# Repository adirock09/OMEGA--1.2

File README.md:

# OMEGA--1.2<br><br>
<br><br>

This is a Custom Rp2040 Chip Based MicroPad , It has 9 Switches , a roter encode and a oled screen . We used matrix for switches so it uses less gpio pins and it has 4 layers the rotor key is used to change the layers which is displaced on the screen so in total we have  keys output 9x4=36 + 4 outputs from rotor = 40 Outputs.
## Features

- Based on RP2040 Chip
- Has total 40 Outputs
## Firmware
- Firmware is based on QMK.
### Schematic<br><br>
<br><br>

###  PCB Design<br><br>
<br><br>
### Case<br><br>

<br><br>

### 3D Design<br><br>

<br><br>

#  Bill of Materials (BOM)

##  DigiKey Components

| Qty | Manufacturer Part Number | Description | Unit Price (USD) | Total (USD) |
|-----|--------------------------|-------------|------------------|-------------|
| 2 | C0402C105K9PACTU | 1µF 6.3V X5R Capacitor (0402) | 0.08000 | 0.16 |
| 11 | 0402B104K160CT | 0.1µF 16V X7R Capacitor (0402) | 0.00300 | 0.03 |
| 2 | LMK107BBJ106MALT | 10µF 10V X5R Capacitor (0603) | 0.08000 | 0.16 |
| 2 | CL05C330JB5NNNC | 33pF 50V C0G Capacitor (0402) | 0.10000 | 0.20 |
| 1 | USB4215-03-A | USB Type-C Receptacle (USB 2.0) | 0.49000 | 0.49 |
| 2 | RC0402FR-075K1L | 5.1KΩ 1% Resistor (0402) | 0.10000 | 0.20 |
| 2 | ERA-2AEB273X | 27KΩ 0.1% Resistor (0402) | 0.10000 | 0.20 |
| 1 | 18996 | 0.91" OLED Display Module | 1.95 | 1.95 |
| 2 | RMCF0603FT1K00 | 1KΩ 1% Resistor (0603) | 0.10000 | 0.20 |
| 1 | RC0201FR-0710KL | 10KΩ 1% Resistor (0201) | 0.10000 | 0.10 |
| 1 | SW-PB9-AB00AQE-5 | Subminiature Pushbutton Switch | 3.39000 | 3.39 |
| 1 | SC0914(13) | RP2040 Microcontroller (QFN-56) | 0.70000 | 0.70 |
| 1 | MCP1700T-3302E/TT | 3.3V 250mA Linear Voltage Regulator | 0.51000 | 0.51 |
| 1 | AT24CS02-SSHM-T | 2Kbit I2C EEPROM | 0.31000 | 0.31 |
| 1 | STDCRA3-8M | 8MHz SMD Crystal | 0.84000 | 0.84 |
| 1 | 183031570409 | M3 Hex Socket Cap Screw | 5.05000 | 5.05 |
| 1 | 5009 | DSA Keycap Set (MX Compatible) | 5.95000 | 5.95 |
| 5 | DV-M30-TH | M3 Heat-Set Thread Insert | 0.18200 | 0.91 |
| 9 | MX2A-71NW | Cherry MX Silent Red Switch | 1.95000 | 17.55 |
| 10 | 1N4148 | Signal Diode 100V 200mA | 0.03900 | 0.39 |
| 1 | 6071183 | Rotary Encoder (BCG13 Series) | 2.44000 | 2.44 |

---

##  Manufacturing & Shipping

| Item | Cost (USD) |
|------|------------|
| DigiKey Shipping  | 20.00 |
| JLCPCB – PCB Fabrication + Stencil | 7.01 |
| JLCPCB Shipping - Coupons | 8.16 |

---

#  Total Project Cost

| Category | Cost (USD) |
|----------|------------|
| DigiKey Components | 41.73 |
| DigiKey Shipping | 20.00 |
| JLCPCB PCB + Stencil | 7.01 |
| JLCPCB Shipping - Coupons | 8.16|
| **Grand Total** | **76.9 USD** |

---

##  Final Total: **$76.9 USD**

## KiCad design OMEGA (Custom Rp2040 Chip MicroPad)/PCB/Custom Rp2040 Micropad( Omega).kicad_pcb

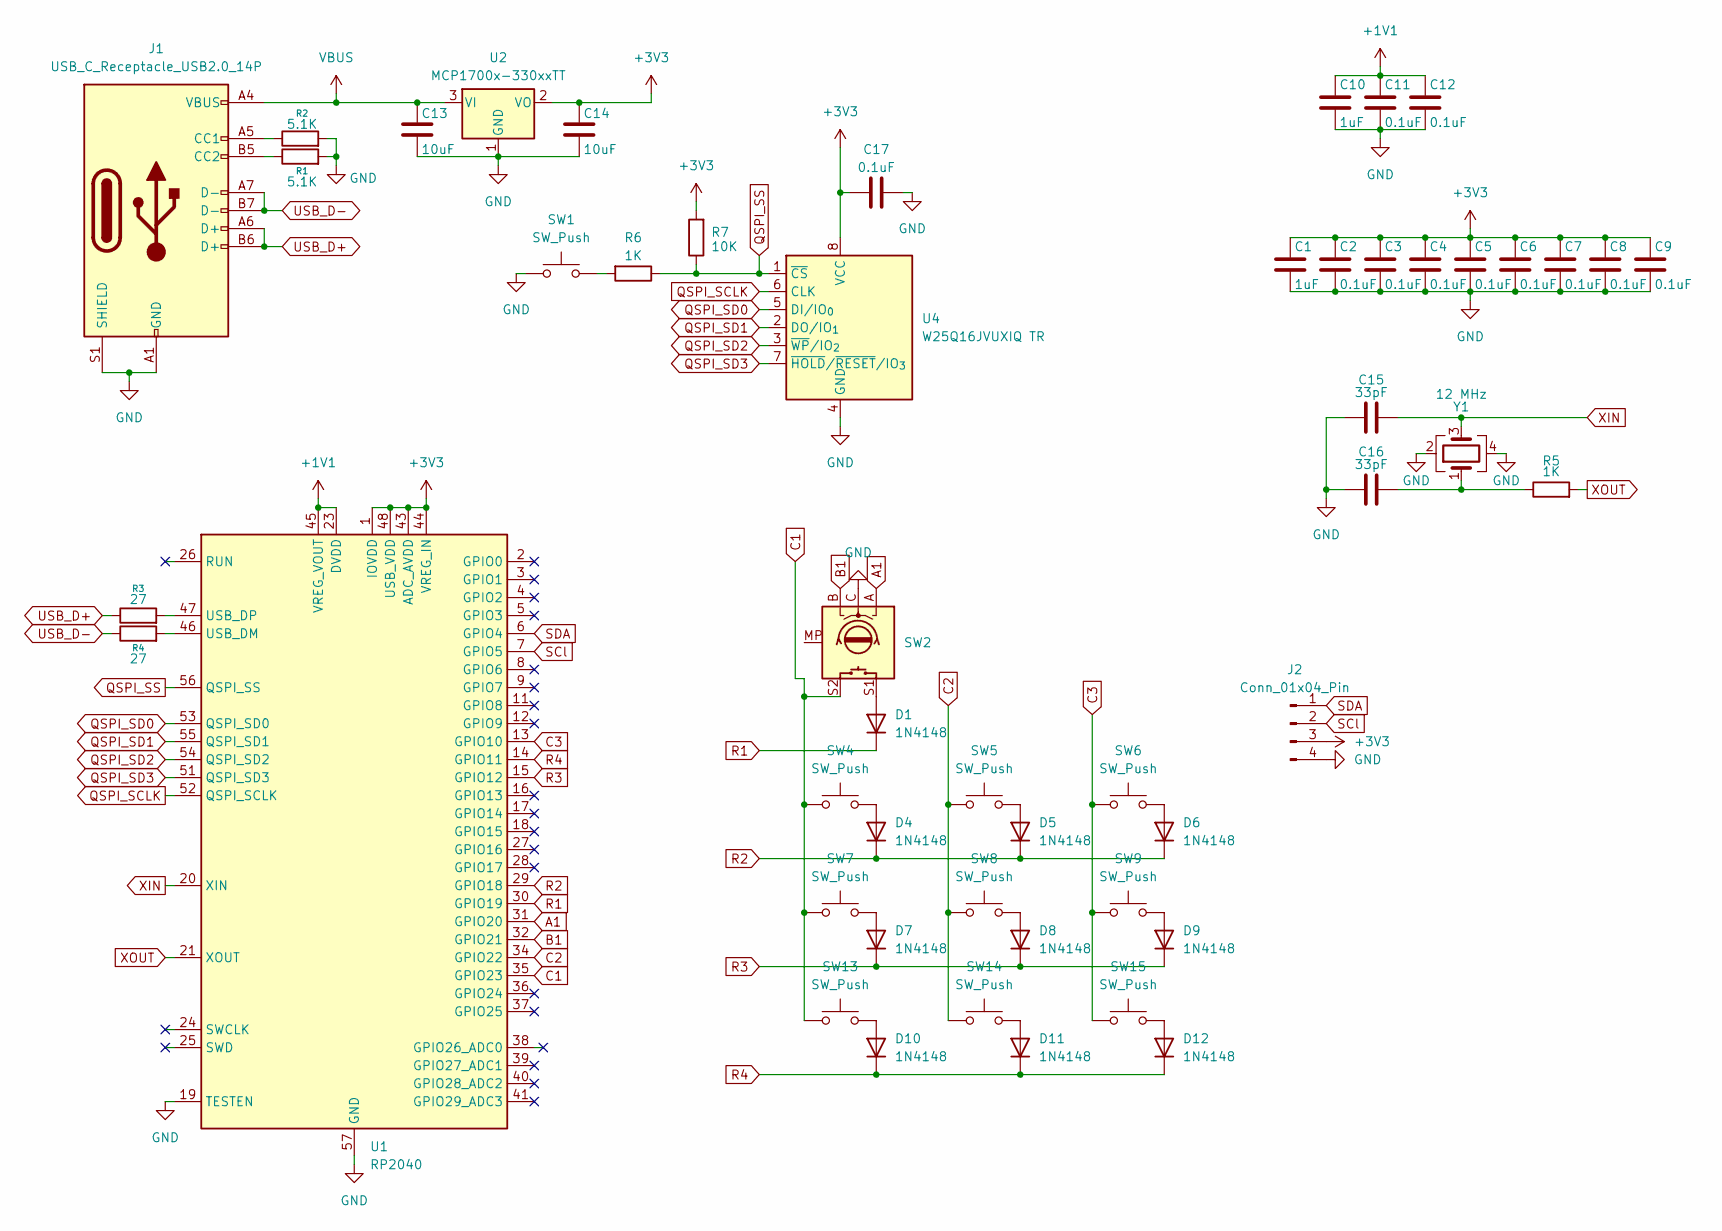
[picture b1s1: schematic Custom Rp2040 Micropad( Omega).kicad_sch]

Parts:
C1, C10: 1uF; C_0402_1005Metric
C2, C3, C4, C5, C6, C7, C8, C9, C11, C12, C17: 0.1uF; C_0402_1005Metric
C13, C14: 10uF; C_0603_1608Metric
C15, C16: 33pF; C_0402_1005Metric
D1, D4, D5, D6, D7, D8, D9, D10, D11, D12: 1N4148; D_DO-35_SOD27_P7.62mm_Horizontal
J1: USB_C_Receptacle_USB2.0_14P; USB_C_Receptacle_HRO_TYPE-C-31-M-12
J2: Conn_01x04_Pin; OLED_128x32
R1, R2: 5.1K; R_0402_1005Metric
R3, R4: 27; R_0402_1005Metric
R5, R6: 1K; R_0402_1005Metric
R7: 10K; R_0402_1005Metric
SW1: SW_Push; SW_Push_SPST_NO_Alps_SKRK
SW2: RotaryEncoder_Switch_MP; RotaryEncoder_Alps_EC11E-Switch_Vertical_H20mm
SW4, SW5, SW6, SW7, SW8, SW9, SW13, SW14, SW15: SW_Push; SW_Cherry_MX_1.00u_PCB
U1: RP2040; QFN-56-1EP_7x7mm_P0.4mm_EP3.2x3.2mm
U2: MCP1700x-330xxTT; SOT-23
U4: W25Q16JVUXIQ TR; Winbond_USON-8-1EP_3x2mm_P0.5mm_EP0.2x1.6mm
Y1: 12 MHz; Crystal_SMD_3225-4Pin_3.2x2.5mm

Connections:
+1V1: C10.1, C11.1, C12.1, U1.23 (DVDD), U1.45 (VREG_VOUT), U1.50 (DVDD)
+3V3: C1.1, C2.1, C3.1, C4.1, C5.1, C6.1, C7.1, C8.1, C9.1, C14.1, C17.1, J2.3, R7.2, U1.1 (IOVDD), U1.10 (IOVDD), U1.22 (IOVDD), U1.33 (IOVDD), U1.42 (IOVDD), U1.43 (ADC_AVDD), U1.44 (VREG_IN), U1.48 (USB_VDD), U1.49 (IOVDD), U2.2 (VO), U4.8 (VCC)
A1: SW2.A, U1.31 (GPIO20)
B1: SW2.B, U1.32 (GPIO21)
C1: SW2.S2, SW4.1, SW7.1, SW13.1, U1.35 (GPIO23)
C2: SW5.1, SW8.1, SW14.1, U1.34 (GPIO22)
C3: SW6.1, SW9.1, SW15.1, U1.13 (GPIO10)
GND: C1.2, C2.2, C3.2, C4.2, C5.2, C6.2, C7.2, C8.2, C9.2, C10.2, C11.2, C12.2, C13.2, C14.2, C15.1, C16.1, C17.2, J1.A1 (GND), J1.A12 (GND), J1.B1 (GND), J1.B12 (GND), J1.S1 (SHIELD), J2.4, R1.2, R2.2, SW1.1, SW2.C, U1.19 (TESTEN), U1.57 (GND), U2.1 (GND), U4.4 (GND), Y1.2, Y1.4
unnamed: C16.2, R5.1, Y1.1
unnamed: D1.2 (A), SW2.S1
unnamed: D4.2 (A), SW4.2
unnamed: D5.2 (A), SW5.2
unnamed: D6.2 (A), SW6.2
unnamed: D7.2 (A), SW7.2
unnamed: D8.2 (A), SW8.2
unnamed: D9.2 (A), SW9.2
unnamed: D10.2 (A), SW13.2
unnamed: D11.2 (A), SW14.2
unnamed: D12.2 (A), SW15.2
unnamed: J1.A5 (CC1), R2.1
unnamed: J1.B5 (CC2), R1.1
unnamed: R6.2, SW1.2
unnamed: R4.2, U1.46 (USB_DM)
unnamed: R3.2, U1.47 (USB_DP)
QSPI_SCLK: U1.52 (QSPI_SCLK), U4.6 (CLK)
QSPI_SD0: U1.53 (QSPI_SD0), U4.5 (DI/IO_{0})
QSPI_SD1: U1.55 (QSPI_SD1), U4.2 (DO/IO_{1})
QSPI_SD2: U1.54 (QSPI_SD2), U4.3 (~WP/IO_{2})
QSPI_SD3: U1.51 (QSPI_SD3), U4.7 (~HOLD/~RESET/IO_{3})
QSPI_SS: R6.1, R7.1, U1.56 (QSPI_SS), U4.1 (~CS)
R1: D1.1 (K), U1.30 (GPIO19)
R2: D4.1 (K), D5.1 (K), D6.1 (K), U1.29 (GPIO18)
R3: D7.1 (K), D8.1 (K), D9.1 (K), U1.15 (GPIO12)
R4: D10.1 (K), D11.1 (K), D12.1 (K), U1.14 (GPIO11)
SCl: J2.2, U1.7 (GPIO5)
SDA: J2.1, U1.6 (GPIO4)
USB_D+: J1.A6 (D+), J1.B6 (D+), R3.1
USB_D-: J1.A7 (D-), J1.B7 (D-), R4.1
VBUS: C13.1, J1.A4 (VBUS), J1.A9 (VBUS), J1.B4 (VBUS), J1.B9 (VBUS), U2.3 (VI)
XIN: C15.2, U1.20 (XIN), Y1.3
XOUT: R5.2, U1.21 (XOUT)

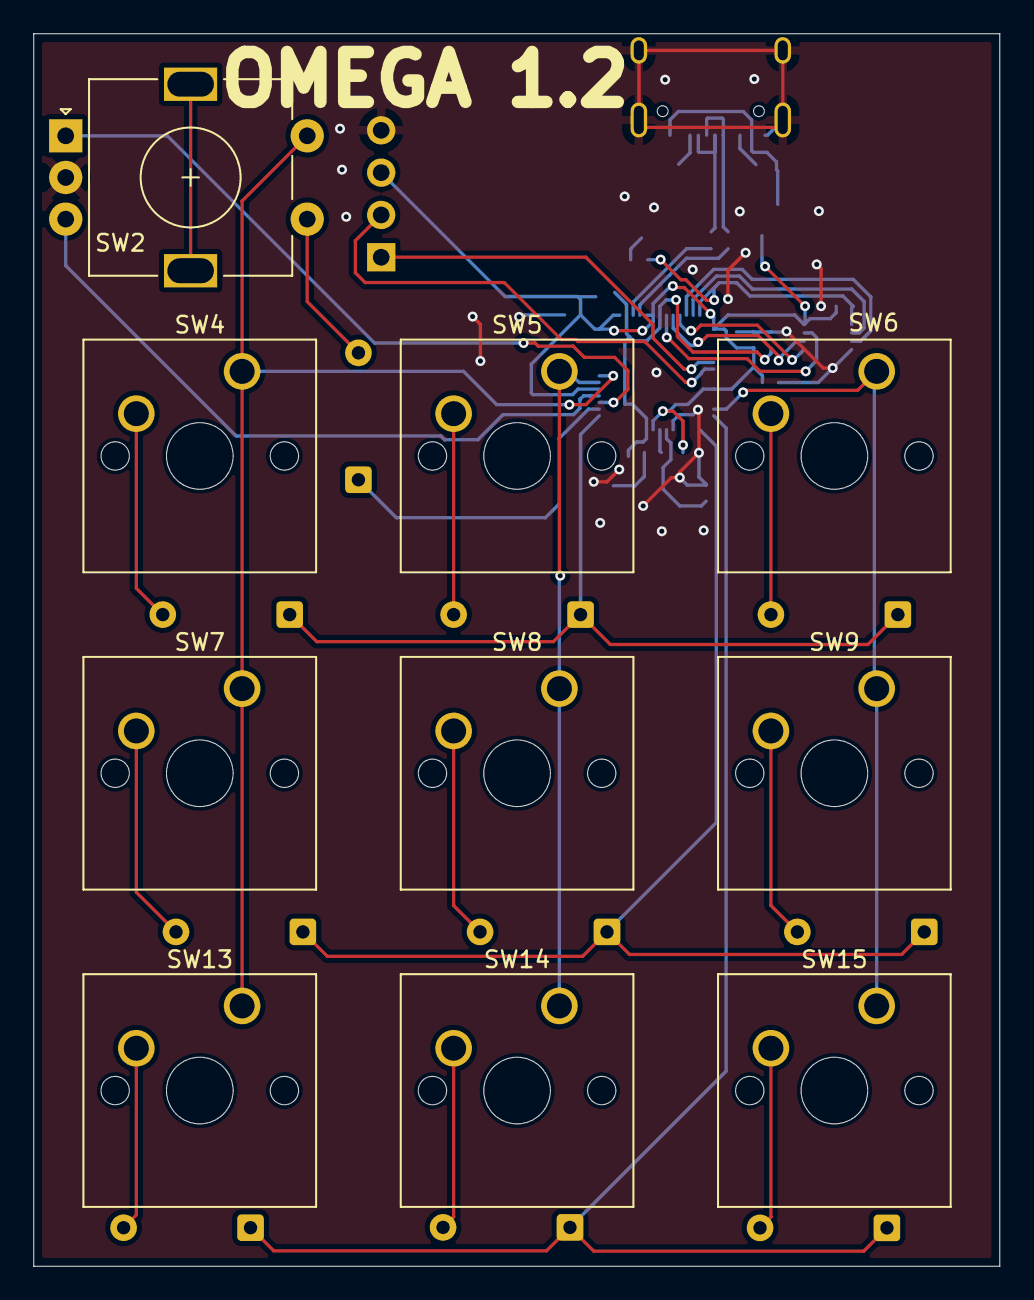
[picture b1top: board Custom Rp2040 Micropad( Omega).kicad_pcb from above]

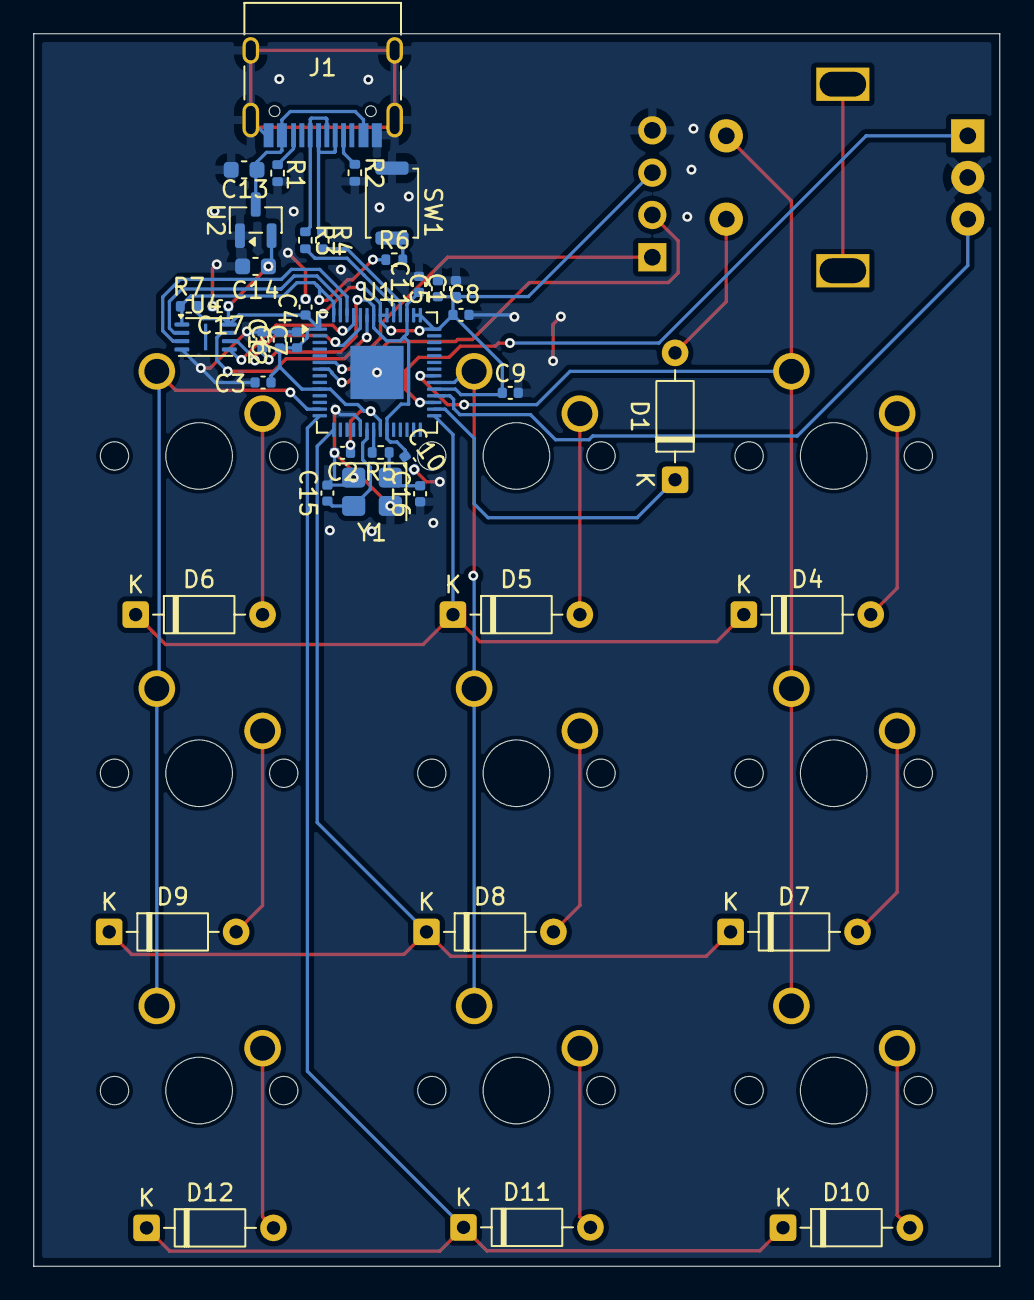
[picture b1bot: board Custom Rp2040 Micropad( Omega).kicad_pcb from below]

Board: 2 copper layers, 58.0 x 74.0 mm, 51 parts (40 on the bottom side), 41 nets.
